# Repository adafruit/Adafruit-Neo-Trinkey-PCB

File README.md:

## Adafruit Neo Trinkey PCB

<a href="http://www.adafruit.com/products/4870"><br/>
Click here to purchase one from the Adafruit shop</a>

PCB files for the Adafruit Neo Trinkey. 

Format is EagleCAD schematic and board layout
* https://www.adafruit.com/product/4870

### Description

It's half USB Key, half Adafruit Trinket...it's Neo Trinkey, the circuit board with a Trinket M0 heart and  four RGB NeoPixels for customizable glow. We were inspired by some USB key flashlight boards that would turn any battery pack into an LED torch. So we thought, hey what if we made something like that but with fully programmable color NeoPixels? And this is what we came up with!

The PCB is designed to slip into any USB A port on a computer or laptop. There's an ATSAMD21 microcontroller on board with just enough circuitry to keep it happy. One pin of the microcontroller connects to the four NeoPixel LEDs. Two other pins are used as capacitive touch inputs on the end - if you look carefully you can see the slotted end has left and right touch pads. A reset button lets you enter bootloader mode if necessary. That's it!

The SAMD21 can run CircuitPython or Arduino very nicely - with existing NeoPixel and our FreeTouch libraries for the capacitive touch input. Over the USB connection you can have serial, MIDI or HID connectivity. The Neo Trinkey is perfect for simple projects that can use a few user inputs and colorful outputs. Maybe you'll set it up as a simple status notifier, or stretch-break timer, or a macro keypad, or a random color generator, or, hey you could still make it into an LED flashlight if you wanted!

We think its just an adorable little board, small and durable and inexpensive enough that it could be a first microcontroller board, or inspiration for advanced developers to make something simple and fun.

* ATSAMD21E18 32-bit Cortex M0+ - 48 MHz 32 bit processor with 256KB Flash and 32 KB RAM
* Native USB supported by every OS - can be used in Arduino or CircuitPython as USB serial console, MIDI, Keyboard/Mouse HID, even a little disk drive for storing Python scripts.
* Can be used with Arduino IDE or CircuitPython
* Four RGB NeoPixel LEDs
* Two Capacitive Touch pads
* Reset switch for starting your project code over or entering bootloader mode
* Slim and cute, keychain-friendly!

### License

Adafruit invests time and resources providing this open source design, please support Adafruit and open-source hardware by purchasing products from [Adafruit](https://www.adafruit.com)!

Designed by Limor Fried/Ladyada for Adafruit Industries.

Creative Commons Attribution/Share-Alike, all text above must be included in any redistribution. 
See license.txt for additional details.

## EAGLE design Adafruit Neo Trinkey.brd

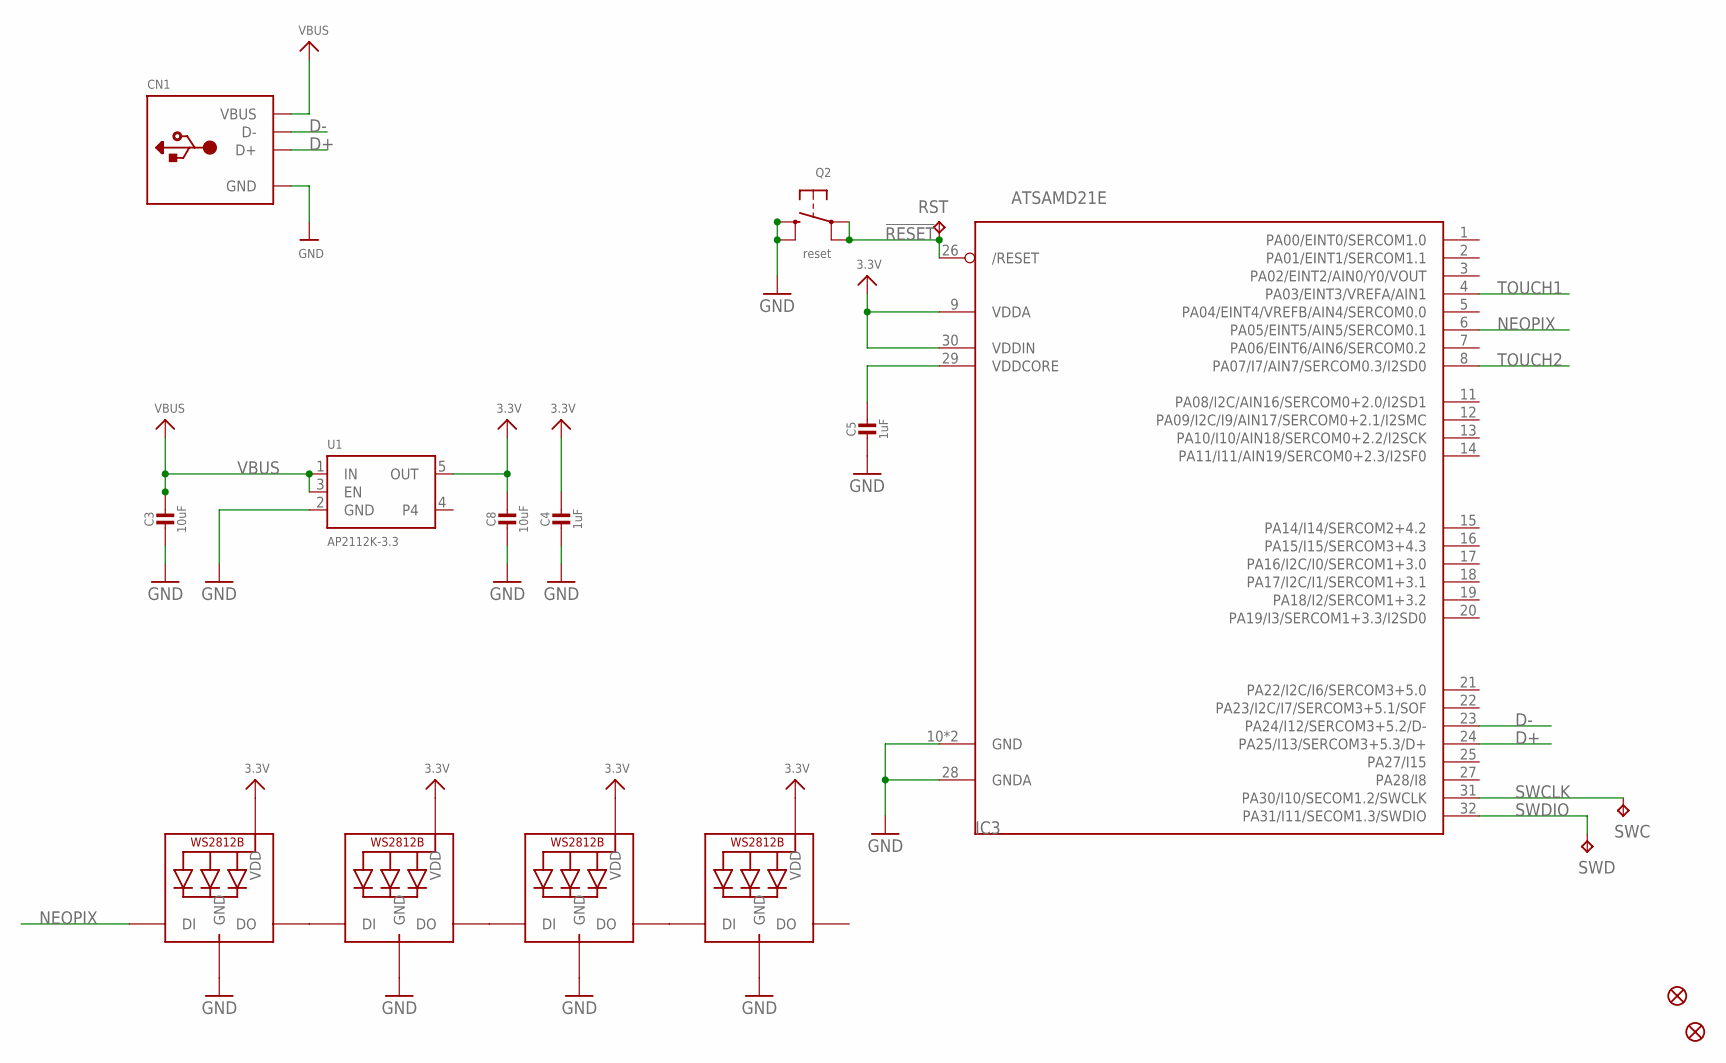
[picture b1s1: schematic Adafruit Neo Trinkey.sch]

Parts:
C3, C8: 10uF; 0805-NO
C4, C5: 1uF; 0603-NO
CN1: USB_TYPEAPCB; USBA_PCB
FID1, FID2: FIDUCIAL_1MM
IC3: ATSAMD21E; QFN32_5MM
LED1, LED2, LED3, LED4: WS2812B3535; LED3535
Q2: reset; BTN_KMR2_4.6X2.8
RST: TPTP16R; TP16R
SWC: TPTP15R; TP15R
SWD: TPTP16R; TP16R
U1: AP2112K-3.3; SOT23-5

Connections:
3.3V: C4.1, C8.1, IC3.9 (VDDA), IC3.30 (VDDIN), LED1.2 (VDD), LED2.2 (VDD), LED3.2 (VDD), LED4.2 (VDD), U1.5 (OUT)
!RESET: IC3.26 (/RESET), Q2.A, Q2.A' (P1), RST.TP
D+: CN1.USB_PLUS (D+), IC3.24 (PA25/I13/SERCOM3+5.3/D+)
D-: CN1.USB_NEG (D-), IC3.23 (PA24/I12/SERCOM3+5.2/D-)
GND: C3.2, C4.2, C5.2, C8.2, CN1.GND, IC3.10 (GND), IC3.28 (GNDA), IC3.33 (GND), LED1.4 (GND), LED2.4 (GND), LED3.4 (GND), LED4.4 (GND), Q2.B (S), Q2.B' (S1), U1.2 (GND)
unnamed: LED1.3 (DO), LED2.1 (DI)
unnamed: LED2.3 (DO), LED3.1 (DI)
unnamed: LED3.3 (DO), LED4.1 (DI)
NEOPIX: IC3.6 (PA05/EINT5/AIN5/SERCOM0.1), LED1.1 (DI)
SWCLK: IC3.31 (PA30/I10/SECOM1.2/SWCLK), SWC.TP
SWDIO: IC3.32 (PA31/I11/SECOM1.3/SWDIO), SWD.TP
TOUCH1: IC3.4 (PA03/EINT3/VREFA/AIN1)
TOUCH2: IC3.8 (PA07/I7/AIN7/SERCOM0.3/I2SD0)
VBUS: C3.1, CN1.VCC (VBUS), U1.1 (IN), U1.3 (EN)
VDDCORE1: C5.1, IC3.29 (VDDCORE)

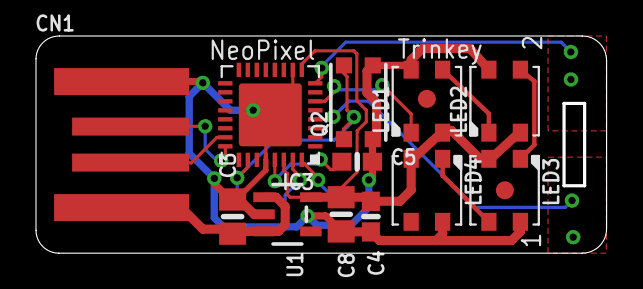
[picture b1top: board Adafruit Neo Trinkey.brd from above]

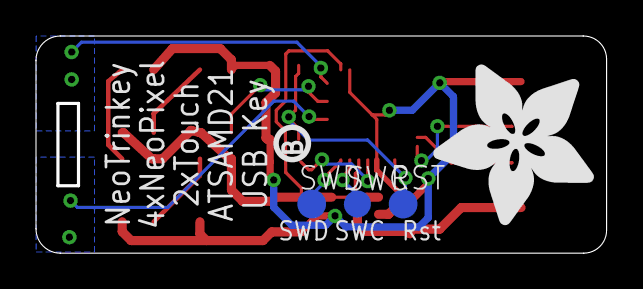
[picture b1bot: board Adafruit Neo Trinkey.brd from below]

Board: 2 copper layers, 31.5 x 11.9 mm, 19 parts (5 on the bottom side), 13 nets.

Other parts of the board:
U$8: PCBFEAT-REV-040
U$10: ADAFRUIT_9MM

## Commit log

2021-04-06 Adding board files.
2021-05-21 Add pinout diagram.
2025-07-15 swap touch 1 and touch 2

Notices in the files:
parts and their libraries:
microbuilder: This work is placed in the public domain, and may be freely used for commercial and non-commercial work with the following conditions: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
